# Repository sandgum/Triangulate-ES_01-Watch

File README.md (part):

# Triangulate ES_01 E-ink Watch

---

An ultra-thin ESP32S3-based smartwatch (at just 5mm thick at its thickest point) which uses an E-ink display and two OLEDs to display information while consuming a small amount of power. The main E-ink panel is touch-enabled, with the two additional OLED panels above and below it displaying auxiliary information, such as notifications, background activities etc. 
The watch has built-in heart rate and spO2 sensing via an Analog Devices MAX30102, high-precision smart movement sensing via a Bosch BH260AP IMU and a Bosch BMP585 barometric pressure sensor.

*ACKNOWLEDGMENT: Most of the materials and the human hand model you see in the renders are not my own work, but is Royalty-free or CC0 licensed work legitimately downloaded from BlenderKit using their free plan*

---

To top it all off, the ES_01 is completely workout-friendly, with rubberised sides and no pesky side buttons that get pressed mid-pushup (Every physical input is at the top of the watch)!
The watch features a sleek design, with each component being laid out single file and in its own separate segment of the watch. These segments can all bend around the watch, preserving a uniform thickness all around, which also adds the benefit of being aesthetically pleasing.
The main microcontroller running the watch is an Espressif ESP32-S3 running with Bluetooth LE capabilities, which also allow for it to sync with a smartphone to relay notifications, workout, and weather data etc. through firmware based on ESP-IDF and host smartphone software for iPhone based on Swift (Coming soon, and Android support will come later!)

---

## PCB:

- 4 layers
- Flex PCB
- Single-sided component placement
- 0.2mm board thickness
- Added 0.1mm FR4 stiffeners
- All resistors and capacitors are 0402 size

### Schematics:

### PCB Layout and render:

*Render is out of date*

---

## Enclosure:

- Main cases and top plates of each segment 3D printed using PLA
- Bottom plates for OLED segments are CNC machined from 6061 Aluminium by JLCCNC (can substitute with any rigid material or also with SLA/MSLA printed resin)
- Bottom plate for main E-ink segment 3D printed using an SLM printer in 316L stainless steel (can substitute with other rigid metal with high thermal conductivity)
- Side flexible pieces printed in TPU by an FDM 3D printer

---

## Assembly instructions:

### To manufacture the PCB, refer to the instructions [here](PCB/README.md)

1. Use the solder stencil to squeegee solder paste onto main PCB
2. Place each component onto its respective pads on the main PCB
3. Use a hotplate or a reflow oven to reflow the solder paste underneath the components
4. Hand-solder a thin insulated wire (enamel insulated or rubber insulated) connecting the pads "BATT1_WIRE" together on the PCB
5. Create a solder bridge connecting the pads "GND_TO_GNDIO" and "GNDIO_TO_GND"
6. Create a solder bridge connecting the pads "GND_TO_GNDPWR" and "GNDPWR_TO_GND"
7. Assemble the two "end battery" segments by threading battery wires through them, placing the battery in and attaching the top plates to their respective main cases with superglue
8. Assemble the other battery segment and the haptic module segment in the same way, but thread the "end battery" wires through the dedicated channels in these segments, you should have two sets of two segments with four wires coming out of each set of segments
9. Take the main cases of the OLED modules and superglue the OLED displays into the top of each, making sure the flex cables poke through their dedicated holes
10. Do the same with the E-ink segment and the E-ink display
11. Attach each remaining top plate to its respective main case using superglue
12. Place and superglue the main Flex PCB into the bottom of the E-ink segment and the two OLED segments. The back of the PCB should face the displays
13. Thread the wires from the two sets of segments from step 8 through the holes in the side of the OLED modules and hand-solder the wires onto their respective pads
14. Plug in the flex cables from each display into thir respective FPC connectors on the main PCB
15. Superglue the bottom panels for the OLED segments onto their respective main cases
16. Apply thermal paste on the ESP32-S3 chip on the main PCB
17. Superglue threaded inserts in the two dedicated holes in the corners of the bottom panel for the E-ink segment
18. Superglue the bottom panel to the main case of the E-ink segment
19. Screw two screws into the holes in the top case of the E-ink segment until they mesh with the threaded inserts from the previous step
20. Take two more screws and cut off their entire threaded sections until just the heads remain. Superglue those heads in the holes in the other two corners of the top panel of the E-ink segment
21. Superglue the side TPU pieces to the sides of all the segments
22. Plug in a patch antenna into the exposed U.FL port on the back of the watch, guide the cable through its designated groove, and stick the patch antenna somewhere on the watch

---

## Bill of materials:

### Electronic Components: (Order quantities account for minimum order quantity of parts from the chosen retailer)

| Manufacturer Part Number | Mfr.                        | Order Qty. | Unit Price(USD) | Ext.Price(USD) | Package                                | Description                                                                                                                | Product Link                                                                                                                                                                                                                                                                                                                                                                                                                                                                                                                                                                                                                                                                                                                                                                                                                                                    |
| ------------------------ | --------------------------- | ---------- | --------------- | -------------- | -------------------------------------- | -------------------------------------------------------------------------------------------------------------------------- | --------------------------------------------------------------------------------------------------------------------------------------------------------------------------------------------------------------------------------------------------------------------------------------------------------------------------------------------------------------------------------------------------------------------------------------------------------------------------------------------------------------------------------------------------------------------------------------------------------------------------------------------------------------------------------------------------------------------------------------------------------------------------------------------------------------------------------------------------------------- |
| CC0402JRNPO9BN110        | YAGEO                       | 100        | 0.0013          | 0.13           | 0402                                   | 11pF �5% 50V Ceramic Capacitor NP0 0402                                                                                    | https://www.lcsc.com/product-detail/C527000.html                                                                                                                                                                                                                                                                                                                                                                                                                                                                                                                                                                                                                                                                                                                                                                                                                |
| GRM155R61E475ME15D       | muRata                      | 20         | 0.0403          | 0.81           | 0402                                   | 4.7uF �20% 25V Ceramic Capacitor X5R 0402                                                                                  | https://www.lcsc.com/product-detail/C2858031.html                                                                                                                                                                                                                                                                                                                                                                                                                                                                                                                                                                                                                                                                                                                                                                                                               |
| ESP32-S3                 | ESPRESSIF                   | 1          | 3.0048          | 3              | QFN-56-EP(7x7)                         | -98.4dBm 150Mbps 2.412GHz~2.484GHz 2.4GHz 3V~3.6V QFN-56-EP(7x7) RF Transceiver ICs RoHS                                   | https://www.lcsc.com/product-detail/C2913192.html                                                                                                                                                                                                                                                                                                                                                                                                                                                                                                                                                                                                                                                                                                                                                                                                               |
| 2328702-6                | TE Connectivity             | 5          | 0.2027          | 1.01           | SMD,P=0.5mm,Surface Mount,Right Angle  | FFC/FPC Connector 6 Position 0.5mm Pitch Double-Sided Contacts, Top and Bottom Entry Surface Mount, Right Angle -40?~+85?  | https://www.lcsc.com/product-detail/C3151647.html                                                                                                                                                                                                                                                                                                                                                                                                                                                                                                                                                                                                                                                                                                                                                                                                               |
| FFC2B28-24-G             | Global Connector Technology | 1          | 0.5754          | 0.58           | SMD,P=0.5mm,Surface Mount,Right Angle  | FFC/FPC Connector 24 Position 0.5mm Pitch Double-Sided Contacts, Top and Bottom Entry Surface Mount, Right Angle -25?~+85? | https://www.lcsc.com/product-detail/C3151659.html                                                                                                                                                                                                                                                                                                                                                                                                                                                                                                                                                                                                                                                                                                                                                                                                               |
| BHI260AP                 | Bosch                       | 1          | 9.8338          | 9.83           | LGA-44                                 | LGA-44 IMUs (Inertial Measurement Units) RoHS                                                                              | https://www.lcsc.com/product-detail/C3288651.html                                                                                                                                                                                                                                                                                                                                                                                                                                                                                                                                                                                                                                                                                                                                                                                                               |
| SI1308EDL-T1-GE3         | VISHAY                      | 5          | 0.1543          | 0.77           | SOT-323                                | N-Channel 30V 1.5A 0.4W Surface Mount SOT-323                                                                              | https://www.lcsc.com/product-detail/C469327.html                                                                                                                                                                                                                                                                                                                                                                                                                                                                                                                                                                                                                                                                                                                                                                                                                |
| XC6206P302MR             | HXY MOSFET                  | 50         | 0.0176          | 0.88           | SOT-23                                 | Linear Voltage Regulator IC Positive Fixed 1 Output 300mA SOT-23                                                           | https://www.lcsc.com/product-detail/C5148691.html                                                                                                                                                                                                                                                                                                                                                                                                                                                                                                                                                                                                                                                                                                                                                                                                               |
| MBR0530                  | Huixin                      | 20         | 0.0296          | 0.59           | SOD-123                                | 5.5A 1 Independent 30V 500mV@500mA 500mA SOD-123 Single Diodes RoHS                                                        | https://www.lcsc.com/product-detail/C49435625.html                                                                                                                                                                                                                                                                                                                                                                                                                                                                                                                                                                                                                                                                                                                                                                                                              |
| 0402WGF1004TCE           | UNI-ROYAL                   | 100        | 0.0008          | 0.08           | 0402                                   | 1M? �1% 62.5mW 0402 Thick Film Resistor                                                                                    | https://www.lcsc.com/product-detail/C26083.html                                                                                                                                                                                                                                                                                                                                                                                                                                                                                                                                                                                                                                                                                                                                                                                                                 |
| CL05A105KA5NQNC          | Samsung Electro-Mechanics   | 100        | 0.0033          | 0.33           | 0402                                   | 1uF �10% 25V Ceramic Capacitor X5R 0402                                                                                    | https://www.lcsc.com/product-detail/C52923.html                                                                                                                                                                                                                                                                                                                                                                                                                                                                                                                                                                                                                                                                                                                                                                                                                 |
| XL2EL89CPI-111YLC-40M    | YXC Crystal Oscillators     | 10         | 0.0619          | 0.62           | SMD3225-4P                             | Crystal 40MHz �10ppm 15pF SMD3225-4P                                                                                       | https://www.lcsc.com/product-detail/C5444549.html                                                                                                                                                                                                                                                                                                                                                                                                                                                                                                                                                                                                                                                                                                                                                                                                               |
| TS-1088-AR02016          | XUNPU                       | 10         | 0.0455          | 0.46           | SMD,4x3mm                              | Tactile Switch SPST 160gf 2mm SMD (SMT) Tab 4mm x 3mm Surface Mount                                                        | https://www.lcsc.com/product-detail/C720477.html                                                                                                                                                                                                                                                                                                                                                                                                                                                                                                                                                                                                                                                                                                                                                                                                                |
| BSS138                   | R+O                         | 50         | 0.0172          | 0.86           | SOT-23                                 | N-Channel 50V 340mA 350mW Surface Mount SOT-23                                                                             | https://www.lcsc.com/product-detail/C7420339.html                                                                                                                                                                                                                                                                                                                                                                                                                                                                                                                                                                                                                                                                                                                                                                                                               |
| TCR2EF33,LM(CT           | TOSHIBA                     | 5          | 0.1077          | 0.54           | TSOT-25                                | 3.3V 5.5V Positive Fixed TSOT-25 Voltage Regulators - Linear, Low Drop Out (LDO) Regulators RoHS                           | https://www.lcsc.com/product-detail/C843273.html                                                                                                                                                                                                                                                                                                                                                                                                                                                                                                                                                                                                                                                                                                                                                                                                                |
| LQG15HS3N3S02D           | muRata                      | 100        | 0.0079          | 0.79           | 0402                                   | 800mA 3.3nH 170m? Multilayer inductor 0402 Fixed Inductors RoHS                                                            | https://www.lcsc.com/product-detail/C86064.html                                                                                                                                                                                                                                                                                                                                                                                                                                                                                                                                                                                                                                                                                                                                                                                                                 |
| MRA4003T3G               | onsemi                      | 10         | 0.1152          | 1.15           | SMA(DO-214AC)                          | Diode 300V 1A Surface Mount SMA(DO-214AC)                                                                                  | https://www.lcsc.com/product-detail/C94410.html                                                                                                                                                                                                                                                                                                                                                                                                                                                                                                                                                                                                                                                                                                                                                                                                                 |
| DRV2605LDGSR             | TI                          | 1          | 1.3734          | 1.37           | VSSOP-10-0.5mm                         | I2C VSSOP-10-0.5mm Motor Drivers, Controllers RoHS                                                                         | https://www.lcsc.com/product-detail/C527464.html                                                                                                                                                                                                                                                                                                                                                                                                                                                                                                                                                                                                                                                                                                                                                                                                                |
| LQG15HS2N0S02D           | muRata                      | 100        | 0.0084          | 0.84           | 0402                                   | 900mA 2nH 100m? Multilayer inductor 0402 Fixed Inductors RoHS                                                              | https://www.lcsc.com/product-detail/C18216.html                                                                                                                                                                                                                                                                                                                                                                                                                                                                                                                                                                                                                                                                                                                                                                                                                 |
| 0402WGF5603TCE           | UNI-ROYAL                   | 100        | 0.0006          | 0.06           | 0402                                   | 560k? �1% 62.5mW 0402 Thick Film Resistor                                                                                  | https://www.lcsc.com/product-detail/C132339.html                                                                                                                                                                                                                                                                                                                                                                                                                                                                                                                                                                                                                                                                                                                                                                                                                |
| CL05B103KB5NNNC          | Samsung Electro-Mechanics   | 100        | 0.0014          | 0.14           | 0402                                   | 10nF �10% 50V Ceramic Capacitor X7R 0402                                                                                   | https://www.lcsc.com/product-detail/C15195.html                                                                                                                                                                                                                                                                                                                                                                                                                                                                                                                                                                                                                                                                                                                                                                                                                 |
| 0402B102K500NT           | FH                          | 100        | 0.0012          | 0.12           | 0402                                   | 1nF �10% 50V Ceramic Capacitor X7R 0402                                                                                    | https://www.lcsc.com/product-detail/C1523.html                                                                                                                                                                                                                                                                                                                                                                                                                                                                                                                                                                                                                                                                                                                                                                                                                  |
| CL05B104KO5NNNC          | Samsung Electro-Mechanics   | 100        | 0.0013          | 0.13           | 0402                                   | 100nF �10% 16V Ceramic Capacitor X7R 0402                                                                                  | https://www.lcsc.com/product-detail/C1525.html                                                                                                                                                                                                                                                                                                                                                                                                                                                                                                                                                                                                                                                                                                                                                                                                                  |
| 0402CG1R0C500NT          | FH                          | 100        | 0.0012          | 0.12           | 0402                                   | 1pF 50V Ceramic Capacitor C0G 0402                                                                                         | https://www.lcsc.com/product-detail/C1550.html                                                                                                                                                                                                                                                                                                                                                                                                                                                                                                                                                                                                                                                                                                                                                                                                                  |
| CL05A106MQ5NUNC          | Samsung Electro-Mechanics   | 100        | 0.0056          | 0.56           | 0402                                   | 10uF �20% 6.3V Ceramic Capacitor X5R 0402                                                                                  | https://www.lcsc.com/product-detail/C15525.html                                                                                                                                                                                                                                                                                                                                                                                                                                                                                                                                                                                                                                                                                                                                                                                                                 |
| CL05B224KO5NNNC          | Samsung Electro-Mechanics   | 100        | 0.0041          | 0.41           | 0402                                   | 220nF �10% 16V Ceramic Capacitor X7R 0402                                                                                  | https://www.lcsc.com/product-detail/C16772.html                                                                                                                                                                                                                                                                                                                                                                                                                                                                                                                                                                                                                                                                                                                                                                                                                 |
| BMP585                   | Bosch                       | 1          | 3.5109          | 3.51           | LGA-9(3.3x3.3)                         | 30Kpa~1.25bar LGA-9(3.3x3.3) Pressure Sensors, Transducers RoHS                                                            | https://www.lcsc.com/product-detail/C18184976.html                                                                                                                                                                                                                                                                                                                                                                                                                                                                                                                                                                                                                                                                                                                                                                                                              |
| LD39200PU33R             | ST                          | 1          | 1.0184          | 1.02           | DFN-6(3x3)                             | 3.3V 6V Positive Fixed DFN-6(3x3) Voltage Regulators - Linear, Low Drop Out (LDO) Regulators RoHS                          | https://www.lcsc.com/product-detail/C222192.html                                                                                                                                                                                                                                                                                                                                                                                                                                                                                                                                                                                                                                                                                                                                                                                                                |
| CL05A475MP5NRNC          | Samsung Electro-Mechanics   | 50         | 0.0055          | 0.28           | 0402                                   | 4.7uF �20% 10V Ceramic Capacitor X5R 0402                                                                                  | https://www.lcsc.com/product-detail/C23733.html                                                                                                                                                                                                                                                                                                                                                                                                                                                                                                                                                                                                                                                                                                                                                                                                                 |
| 0402WGF2201TCE           | UNI-ROYAL                   | 100        | 0.0008          | 0.08           | 0402                                   | 2.2k? �1% 62.5mW 0402 Thick Film Resistor                                                                                  | https://www.lcsc.com/product-detail/C25879.html                                                                                                                                                                                                                                                                                                                                                                                                                                                                                                                                                                                                                                                                                                                                                                                                                 |
| 0402WGF4701TCE           | UNI-ROYAL                   | 100        | 0.0008          | 0.08           | 0402                                   | 4.7k? �1% 62.5mW 0402 Thick Film Resistor                                                                                  | https://www.lcsc.com/product-detail/C25900.html                                                                                                                                                                                                                                                                                                                                                                                                                                                                                                                                                                                                                                                                                                                                                                                                                 |
| ANR4012T470M             | APV                         | 10         | 0.0544          | 0.54           | SMD,4x4mm                              | 500mA 47uH 500mA Magnetic Shielded Inductor �20% SMD,4x4mm Fixed Inductors RoHS                                            | https://www.lcsc.com/product-detail/C7497063.html                                                                                                                                                                                                                                                                                                                                                                                                                                                                                                                                                                                                                                                                                                                                                                                                               |
| MAX30102EFD+T            | MAXIM                       | 1          | 13.0636         | 13.06          | OESIP-14                               | I2C OESIP-14 Specialized Sensors RoHS                                                                                      | https://www.lcsc.com/product-detail/C6454833.html                                                                                                                                                                                                                                                                                                                                                                                                                                                                                                                                                                                                                                                                                                                                                                                                               |
| MAX17048X+T10            | MAXIM                       | 1          | 1.1576          | 1.16           | WLP-8(0.9x1.8)                         | Lithium Battery I2C WLP-8(0.9x1.8) Battery Management RoHS                                                                 | https://www.lcsc.com/product-detail/C7497002.html                                                                                                                                                                                                                                                                                                                                                                                                                                                                                                                                                                                                                                                                                                                                                                                                               |
| 1N4148                   | onsemi                      | 50         | 0.0353          | 1.77           | DO-35                                  | Diode 100V 200mA Through Hole DO-35                                                                                        | https://www.lcsc.com/product-detail/C258182.html                                                                                                                                                                                                                                                                                                                                                                                                                                                                                                                                                                                                                                                                                                                                                                                                                |
| FRC0402F1001TS           | FOJAN                       | 100        | 0.0006          | 0.06           | 0402                                   | 1k? �1% 62.5mW 0402 Thick Film Resistor                                                                                    | https://www.lcsc.com/product-detail/C2906864.html                                                                                                                                                                                                                                                                                                                                                                                                                                                                                                                                                                                                                                                                                                                                                                                                               |
| FRC0402F22R0TS           | FOJAN                       | 100        | 0.0006          | 0.06           | 0402                                   | 22? �1% 62.5mW 0402 Thick Film Resistor                                                                                    | https://www.lcsc.com/product-detail/C2929994.html                                                                                                                                                                                                                                                                                                                                                                                                                                                                                                                                                                                                                                                                                                                                                                                                               |
| FRC0402F2R20TS           | FOJAN                       | 100        | 0.0008          | 0.08           | 0402                                   | 2.2? �1% 62.5mW 0402 Thick Film Resistor                                                                                   | https://www.lcsc.com/product-detail/C2909330.html                                                                                                                                                                                                                                                                                                                                                                                                                                                                                                                                                                                                                                                                                                                                                                                                               |
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
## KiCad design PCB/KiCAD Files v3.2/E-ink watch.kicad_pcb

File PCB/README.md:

# How to Manufacture the PCB

1. Go to the folder `PCB/Production Files`

2. Find the zip file named `ES_01_mainPCB-vxx.zip`

3. Upload the zip file to JLCPCB (or your preferred PCB manufacturing site), DO NOT expand the file

4. If you are using JLCPCB, follow these next instructions:
   
   1. **Set Base Material to Flex**
   
   2. Set Substrate Type to 25um dielectric thickness
   
   3. **Set Layers to 4**
   
   4. Leave Dimensions unchanged (They should be greyed out anyways)
   
   5. **Set PCB Qty to 5**
   
   6. Leave Different Design and Delivery Format unchanged
   
   7. **Set PCB Thickness to 0.2mm**
   
   8. Set Coverlay Color to whatever you want! (Yellow is the cheapest btw)
   
   9. Leave Silkscreen, Copper Type, Surface Finish and Gold Thickness unchanged
   
   10. Leave Outer Copper Weight, Inner Copper Weight, Specify Layer Sequence, Stackup Type, Layer Stackup, Coverlay Thickness and Gold Fingers unchanged
   
   11. Set EDA Software to Other
   
   12. **Set Stiffener to FR4**
   
   13. **Set FR4 Thickness to 0.1mm**
   
   14. Leave Cutting Method and Confirm Production file unchanged
   
   15. Set Mark on PCB to Order Number
   
   16. Leave everything else unchanged
   
   17. At the very bottom, select PCB Stencil. In its settings:
       
       1. Leave Framework, Step Stencil and Nano-coating unchanged
       
       2. **Set Stencil Style to Top only**
       
       3. Leave Dimensions unchanged
       
       4. **Set Stencil Qty to 1**
       
       5. Leave everything else unchanged
   
   18. Click Save to Cart, and you're done!

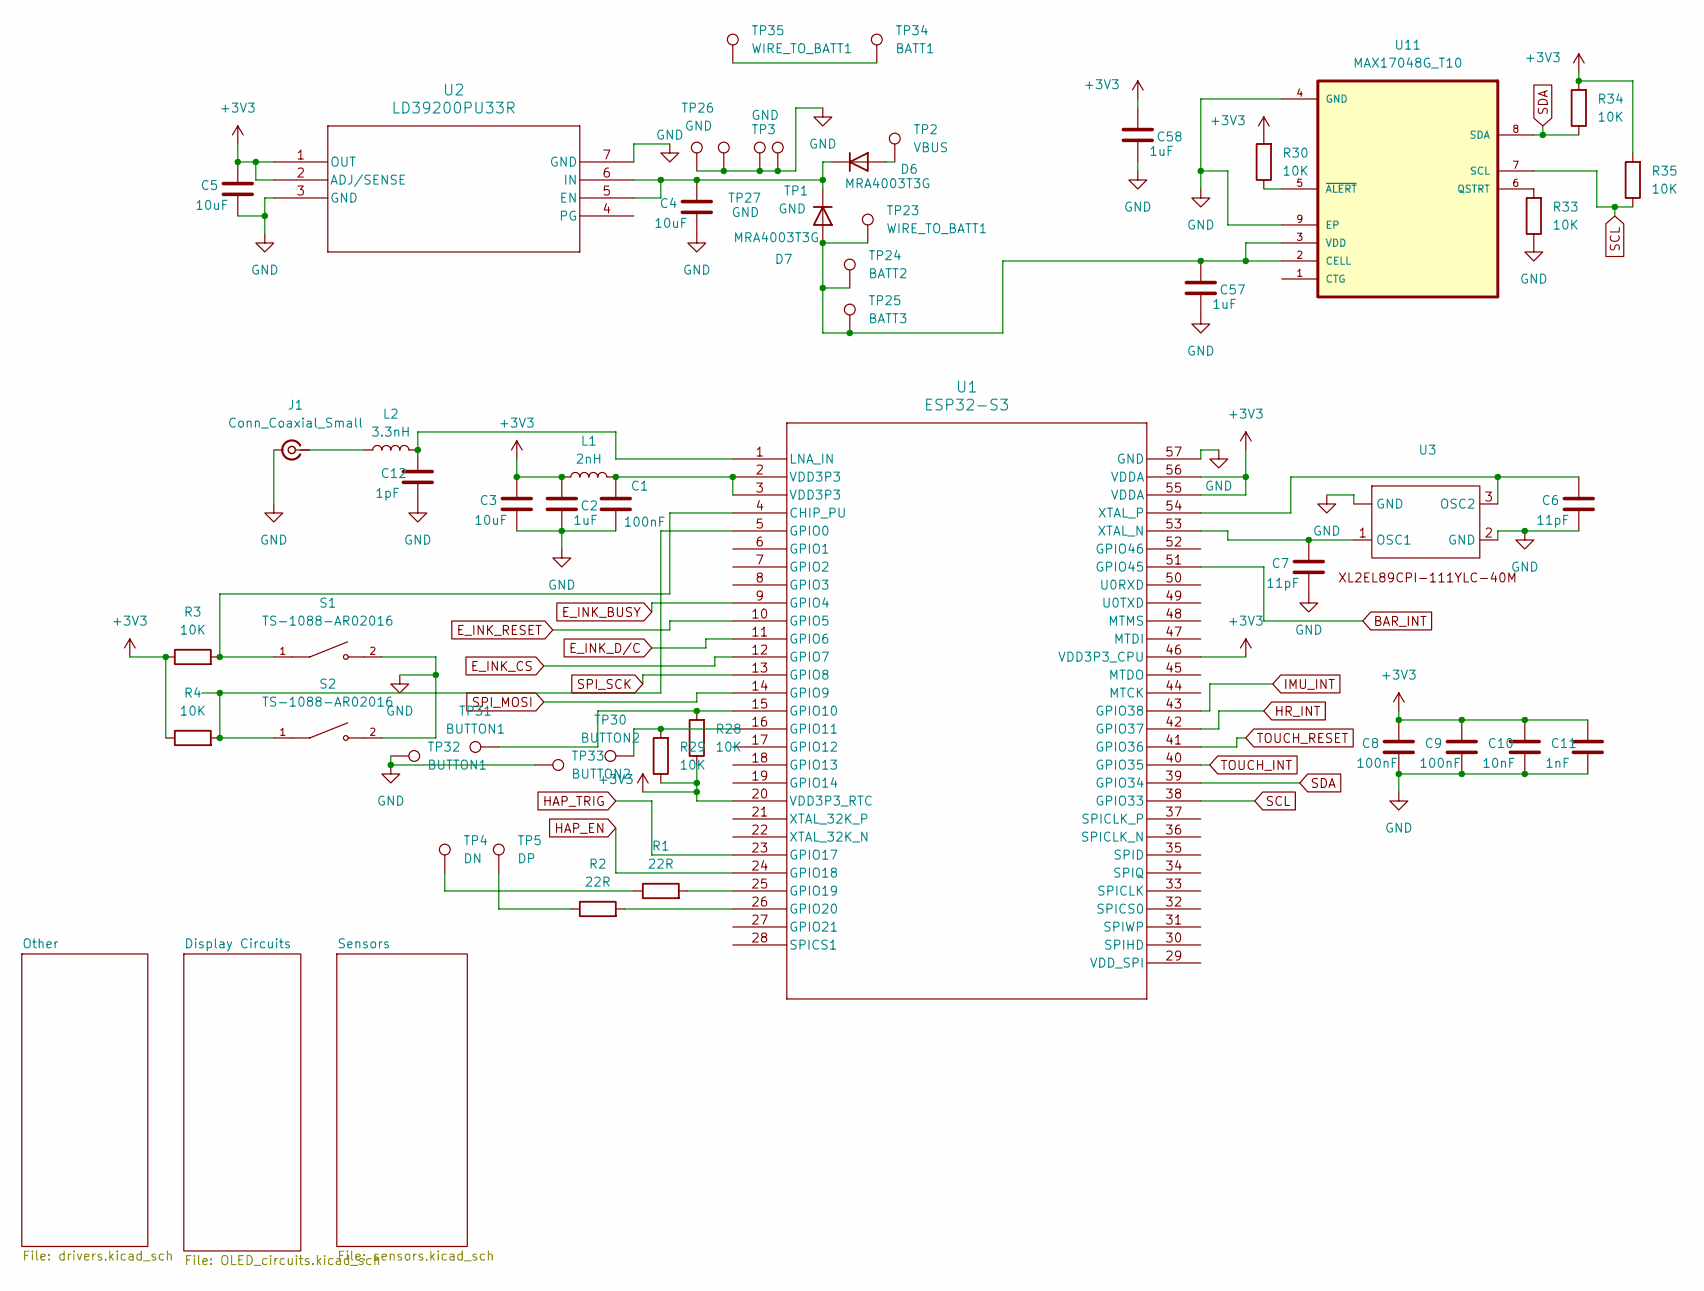
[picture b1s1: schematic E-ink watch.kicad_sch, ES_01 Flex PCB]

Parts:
C1, C8, C9: 100nF; C_0402_1005Metric_Pad0.74x0.62mm_HandSolder
C2, C57, C58: 1uF; C_0402_1005Metric_Pad0.74x0.62mm_HandSolder
C3, C4, C5: 10uF; C_0402_1005Metric_Pad0.74x0.62mm_HandSolder
C6, C7: 11pF; C_0402_1005Metric_Pad0.74x0.62mm_HandSolder
C10: 10nF; C_0402_1005Metric_Pad0.74x0.62mm_HandSolder
C11: 1nF; C_0402_1005Metric_Pad0.74x0.62mm_HandSolder
C12: 1pF; C_0402_1005Metric_Pad0.74x0.62mm_HandSolder
D6, D7: MRA4003T3G; D_SMA
J1: Conn_Coaxial_Small; U.FL_Hirose_U.FL-R-SMT-1_Vertical
L1: 2nH; L_0402_1005Metric_Pad0.77x0.64mm_HandSolder
L2: 3.3nH; L_0402_1005Metric_Pad0.77x0.64mm_HandSolder
R1, R2: 22R; R_0402_1005Metric_Pad0.72x0.64mm_HandSolder
R3, R4, R28, R29, R30, R33, R34, R35: 10K; R_0402_1005Metric_Pad0.72x0.64mm_HandSolder
S1, S2: TS-1088-AR02016; SW_TS-1088-AR02016; PARTREV N/A
TP1, TP3, TP26, TP27: GND; TestPoint_Pad_1.5x1.5mm
TP2: VBUS; TestPoint_Pad_1.5x1.5mm
TP4: DN; TestPoint_Pad_1.5x1.5mm
TP5: DP; TestPoint_Pad_1.5x1.5mm
TP23, TP35: WIRE_TO_BATT1; TestPoint_Pad_1.5x1.5mm
TP24: BATT2; TestPoint_Pad_1.5x1.5mm
TP25: BATT3; TestPoint_Pad_1.5x1.5mm
TP30, TP33: BUTTON2; TestPoint_Pad_1.5x1.5mm
TP31, TP32: BUTTON1; TestPoint_Pad_1.5x1.5mm
TP34: BATT1; TestPoint_Pad_1.5x1.5mm
U1: ESP32-S3; QFN56_7X7_EXP
U2: LD39200PU33R; SON_DFN6_3X3_STM
U3: Untitled
U11: MAX17048G_T10; SON50P200X200X80-9N

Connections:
+3V3: C2.1, C3.1, C5.1, C8.1, C9.1, C10.1, C11.1, C58.1, L1.1, R3.1, R4.1, R28.1, R29.1, R30.2, R34.2, R35.2, U1.20 (VDD3P3_RTC), U1.46 (VDD3P3_CPU), U1.55 (VDDA), U1.56 (VDDA), U2.1 (OUT), U2.2 (ADJ/SENSE); also elsewhere on the board
BAR_INT: U1.51 (GPIO45); also elsewhere on the board
E_INK_BUSY: U1.9 (GPIO4); also elsewhere on the board
E_INK_CS: U1.12 (GPIO7); also elsewhere on the board
E_INK_D/C: U1.11 (GPIO6); also elsewhere on the board
E_INK_RESET: U1.10 (GPIO5); also elsewhere on the board
GND: C1.2, C2.2, C3.2, C4.2, C5.2, C6.2, C7.2, C8.2, C9.2, C10.2, C11.2, C12.2, C57.2, C58.2, J1.2 (Ext), R33.1, S1.2, S2.2, TP1.1, TP3.1, TP26.1, TP27.1, TP32.1, TP33.1, U1.57 (GND), U2.3 (GND), U2.7 (GND), U3. (GND), U3.2 (GND), U11.4 (GND), U11.9 (EP); also elsewhere on the board
HAP_EN: U1.24 (GPIO18); also elsewhere on the board
HAP_TRIG: U1.23 (GPIO17); also elsewhere on the board
HR_INT: U1.42 (GPIO37); also elsewhere on the board
IMU_INT: U1.43 (GPIO38); also elsewhere on the board
unnamed: C1.1, L1.2, U1.2 (VDD3P3), U1.3 (VDD3P3)
unnamed: D6.2 (A), TP2.1
unnamed: C4.1, D6.1 (K), D7.1 (K), U2.5 (EN), U2.6 (IN)
unnamed: C57.1, D7.2 (A), TP23.1, TP24.1, TP25.1, U11.2 (CELL), U11.3 (VDD)
unnamed: J1.1 (In), L2.1
unnamed: R1.1, TP4.1
unnamed: R2.1, TP5.1
unnamed: TP34.1, TP35.1
unnamed: R3.2, S1.1, U1.4 (CHIP_PU)
unnamed: R4.2, S2.1, U1.5 (GPIO0)
unnamed: R28.2, TP31.1, U1.15 (GPIO10)
unnamed: R29.2, TP30.1, U1.16 (GPIO11)
unnamed: R1.2, U1.25 (GPIO19)
unnamed: R2.2, U1.26 (GPIO20)
unnamed: C12.1, L2.2, U1.1 (LNA_IN)
unnamed: C7.1, U1.53 (XTAL_N), U3.1 (OSC1)
unnamed: C6.1, U1.54 (XTAL_P), U3.3 (OSC2)
unnamed: R33.2, U11.6 (QSTRT)
unnamed: R30.1, U11.5 (~ALERT)
SCL: R35.1, U1.38 (GPIO33), U11.7 (SCL); also elsewhere on the board
SDA: R34.1, U1.39 (GPIO34), U11.8 (SDA); also elsewhere on the board
SPI_MOSI: U1.14 (GPIO9); also elsewhere on the board
SPI_SCK: U1.13 (GPIO8); also elsewhere on the board
TOUCH_INT: U1.40 (GPIO35); also elsewhere on the board
TOUCH_RESET: U1.41 (GPIO36); also elsewhere on the board

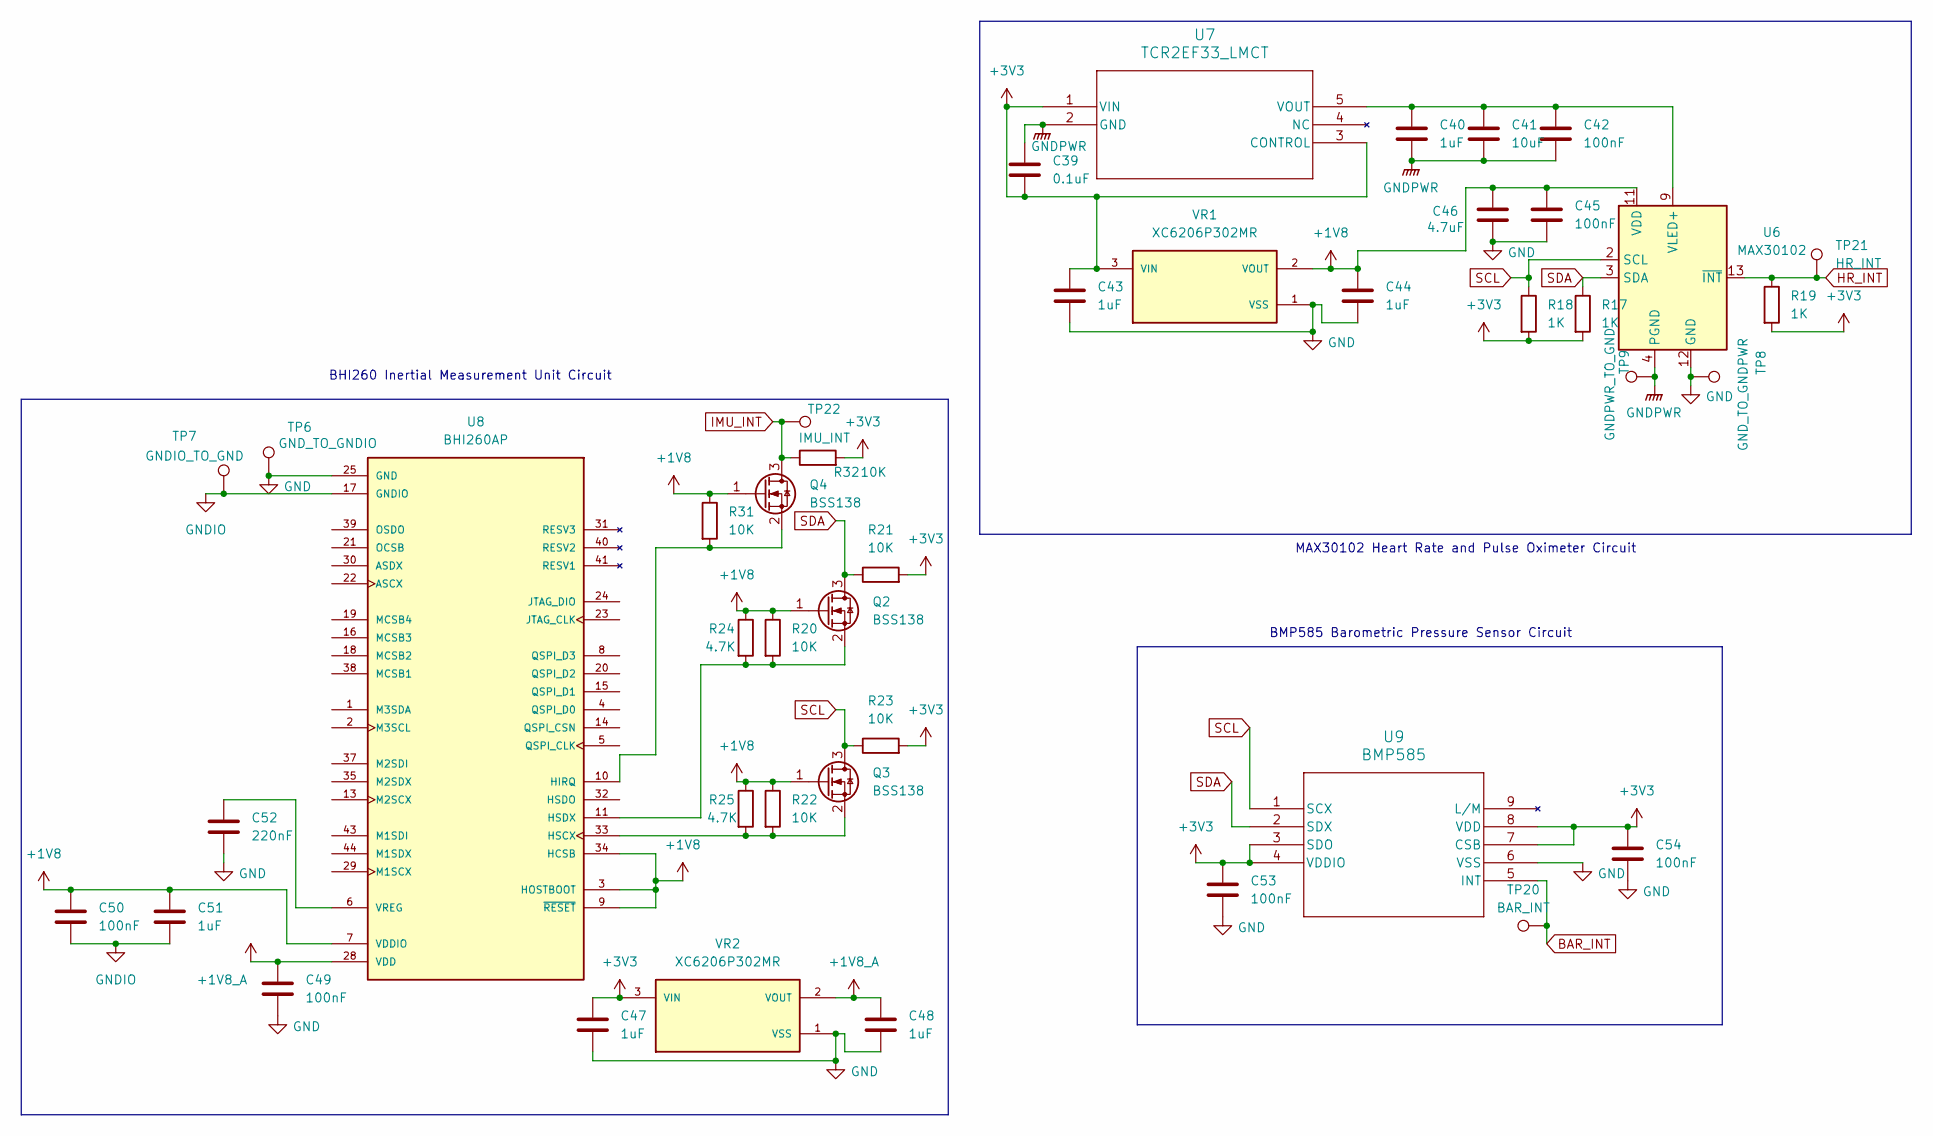
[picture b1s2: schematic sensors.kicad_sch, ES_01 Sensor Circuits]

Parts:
C39: 0.1uF; C_0402_1005Metric_Pad0.74x0.62mm_HandSolder
C40, C43, C44, C47, C48, C51: 1uF; C_0402_1005Metric_Pad0.74x0.62mm_HandSolder
C41: 10uF; C_0402_1005Metric_Pad0.74x0.62mm_HandSolder
C42, C45, C49, C50, C53, C54: 100nF; C_0402_1005Metric_Pad0.74x0.62mm_HandSolder
C46: 4.7uF; C_0402_1005Metric_Pad0.74x0.62mm_HandSolder
C52: 220nF; C_0402_1005Metric_Pad0.74x0.62mm_HandSolder
Q2, Q3, Q4: BSS138; SOT-23
R17, R18, R19: 1K; R_0402_1005Metric_Pad0.72x0.64mm_HandSolder
R20, R21, R22, R23, R31, R32: 10K; R_0402_1005Metric_Pad0.72x0.64mm_HandSolder
R24, R25: 4.7K; R_0402_1005Metric_Pad0.72x0.64mm_HandSolder
TP6: GND_TO_GNDIO; TestPoint_Pad_1.5x1.5mm
TP7: GNDIO_TO_GND; TestPoint_Pad_1.5x1.5mm
TP8: GND_TO_GNDPWR; TestPoint_Pad_1.5x1.5mm
TP9: GNDPWR_TO_GND; TestPoint_Pad_1.5x1.5mm
TP20: BAR_INT; TestPoint_Pad_D1.0mm
TP21: HR_INT; TestPoint_Pad_D1.0mm
TP22: IMU_INT; TestPoint_Pad_D1.0mm
U6: MAX30102; Maxim_OLGA-14_3.3x5.6mm_P0.8mm
U7: TCR2EF33_LMCT; SOT-25 SMV_TOS
U8: BHI260AP; XDCR_BHI260AP; PARTREV 1.1
U9: BMP585; LGA9_BMP585_BOS
VR1, VR2: XC6206P302MR; SOT95P280X130-3N; PARTREV N/A

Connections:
+1V8: C44.1, C45.1, C46.1, C50.1, C51.1, Q2.1 (G), Q3.1 (G), Q4.1 (G), R20.1, R22.1, R24.1, R25.1, R31.1, U6.11 (VDD), U8.3 (HOSTBOOT), U8.7 (VDDIO), U8.9 (~RESET), U8.12 (VDDIO), U8.34 (HCSB), U8.42 (VDDIO), VR1.2 (VOUT)
+1V8_A: C48.1, C49.1, U8.28 (VDD), VR2.2 (VOUT)
+3V3: C39.2, C43.1, C47.1, C53.1, C54.1, R17.2, R18.2, R19.2, R21.2, R23.2, R32.2, U7.1 (VIN), U7.3 (CONTROL), U9.3 (SDO), U9.4 (VDDIO), U9.7 (CSB), U9.8 (VDD), VR1.3 (VIN), VR2.3 (VIN); also elsewhere on the board
BAR_INT: TP20.1, U9.5 (INT); also elsewhere on the board
GND: C43.2, C44.2, C45.2, C46.2, C47.2, C48.2, C49.2, C52.2, C53.2, C54.2, TP6.1, TP8.1, U6.12 (GND), U8.25 (GND), U8.26 (GND), U8.27 (GND), U9.6 (VSS), VR1.1 (VSS), VR2.1 (VSS); also elsewhere on the board
GNDIO: C50.2, C51.2, TP7.1, U8.17 (GNDIO), U8.36 (GNDIO)
GNDPWR: C39.1, C40.2, C41.2, C42.2, TP9.1, U6.4 (PGND), U7.2 (GND)
HR_INT: R19.1, TP21.1, U6.13 (~INT); also elsewhere on the board
IMU_INT: Q4.3 (D), R32.1, TP22.1; also elsewhere on the board
unnamed: Q2.2 (S), R20.2, R24.2, U8.11 (HSDX)
unnamed: Q3.2 (S), R22.2, R25.2, U8.33 (HSCX)
unnamed: Q4.2 (S), R31.2, U8.10 (HIRQ)
unnamed: C40.1, C41.1, C42.1, U6.9 (VLED+), U6.10 (VLED+), U7.5 (VOUT)
unnamed: C52.1, U8.6 (VREG)
SCL: Q3.3 (D), R18.1, R23.1, U6.2 (SCL), U9.1 (SCX); also elsewhere on the board
SDA: Q2.3 (D), R17.1, R21.1, U6.3 (SDA), U9.2 (SDX); also elsewhere on the board

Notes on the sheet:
MAX30102 Heart Rate and Pulse Oximeter Circuit
BHI260 Inertial Measurement Unit Circuit
BMP585 Barometric Pressure Sensor Circuit

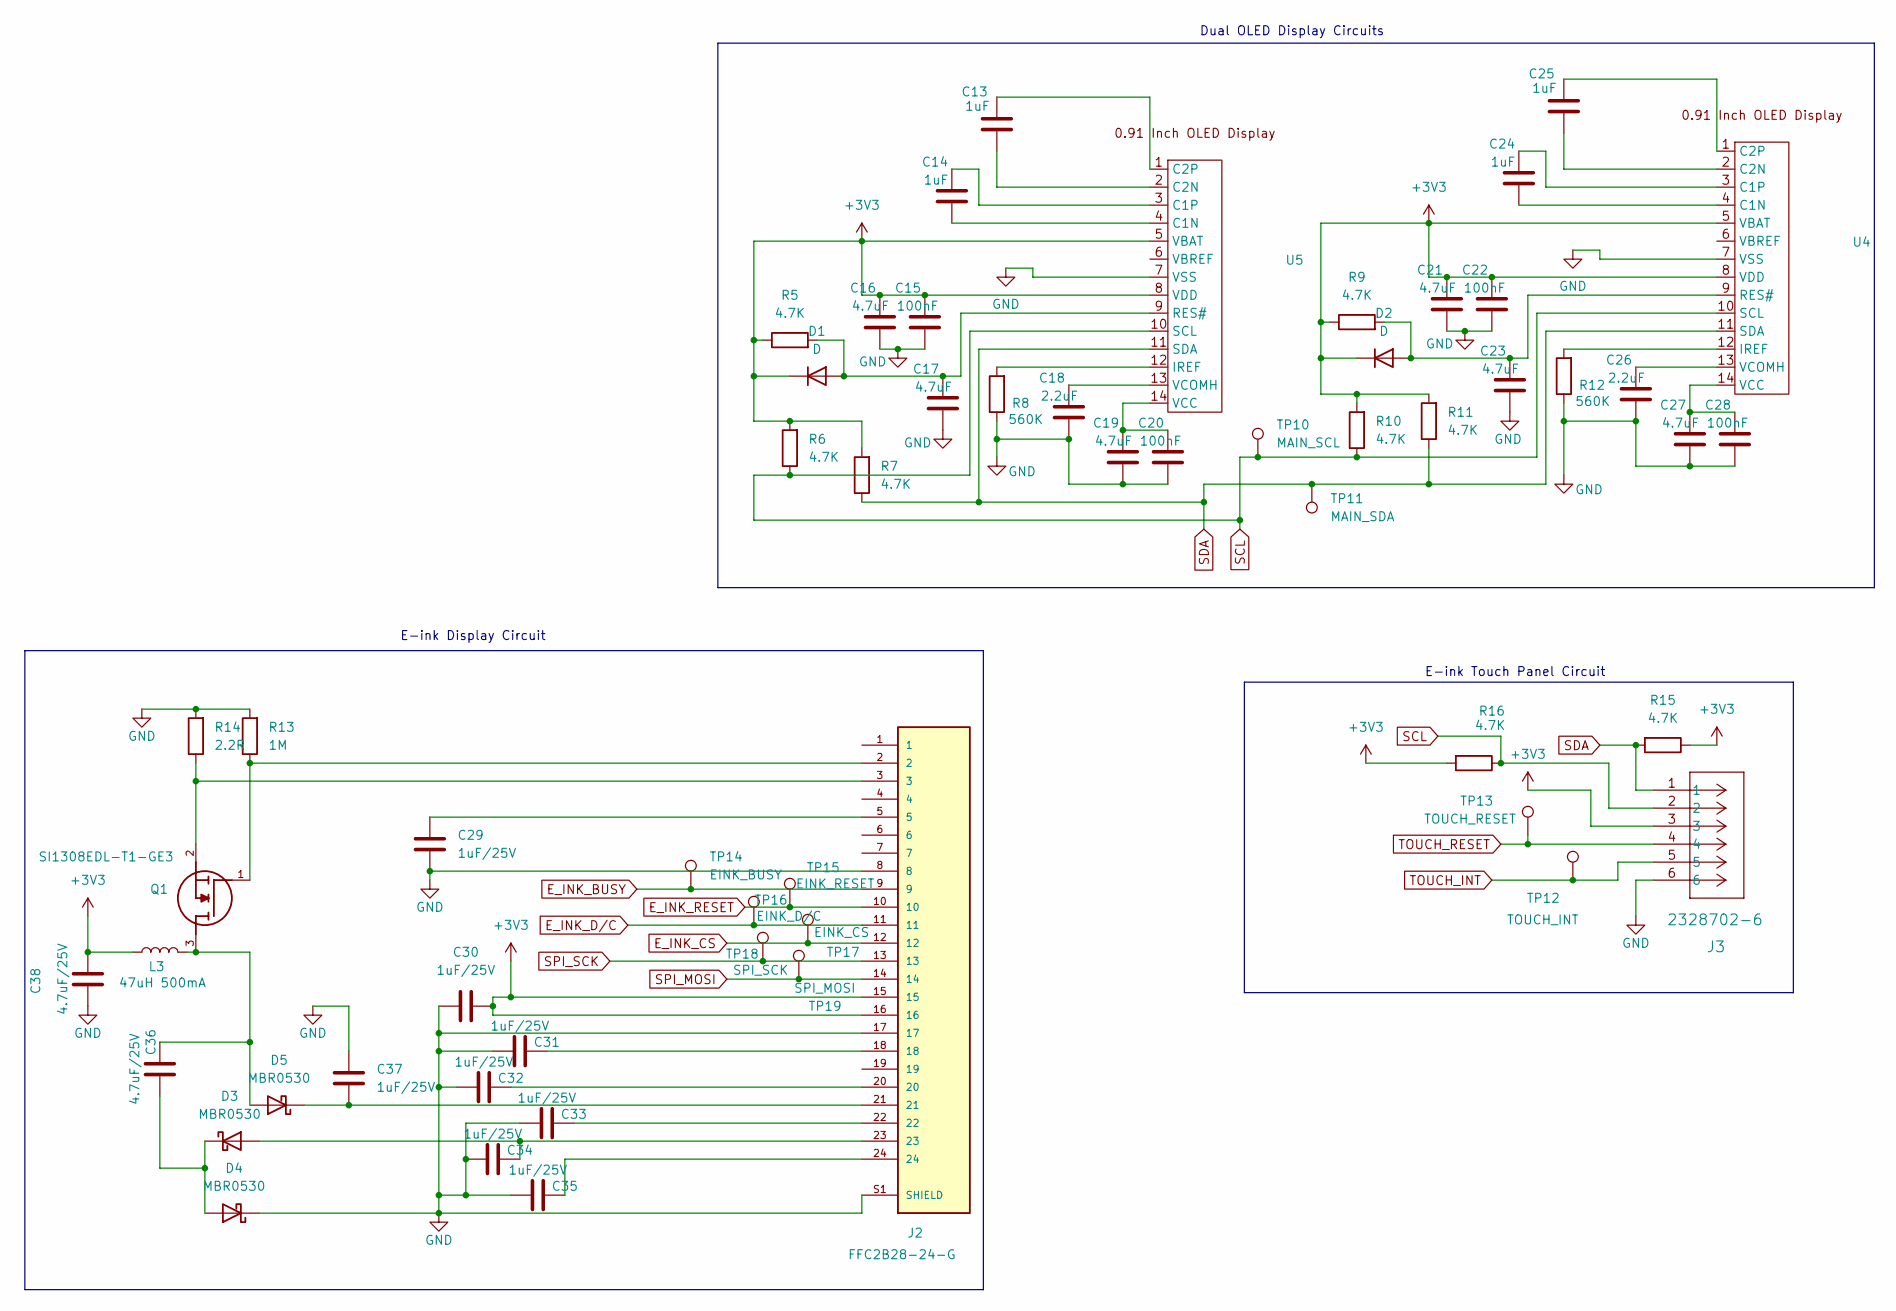
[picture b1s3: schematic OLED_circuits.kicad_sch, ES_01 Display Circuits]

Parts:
C13, C14, C24, C25: 1uF; C_0402_1005Metric_Pad0.74x0.62mm_HandSolder
C15, C20, C22, C28: 100nF; C_0402_1005Metric_Pad0.74x0.62mm_HandSolder
C16, C17, C19, C21, C23, C27: 4.7uF; C_0402_1005Metric_Pad0.74x0.62mm_HandSolder
C18, C26: 2.2uF; C_0402_1005Metric_Pad0.74x0.62mm_HandSolder
C29, C30, C31, C32, C33, C34, C35, C37: 1uF/25V; C_0402_1005Metric_Pad0.74x0.62mm_HandSolder
C36, C38: 4.7uF/25V; C_0402_1005Metric_Pad0.74x0.62mm_HandSolder
D1, D2: D; D_DO-35_SOD27_P7.62mm_Horizontal
D3, D4, D5: MBR0530; D_0805_2012Metric_Pad1.15x1.40mm_HandSolder
J2: FFC2B28-24-G; GCT_FFC2B28-24-G; PARTREV A
J3: 2328702-6; CONN6_2328702-6_TEC
L3: 47uH 500mA; Untitled
Q1: SI1308EDL-T1-GE3; SOT65P210X110-3N; Mouser_Part_Number 78-SI1308EDL-T1-GE3
R5, R6, R7, R9, R10, R11, R15, R16: 4.7K; R_0402_1005Metric_Pad0.72x0.64mm_HandSolder
R8, R12: 560K; R_0402_1005Metric_Pad0.72x0.64mm_HandSolder
R13: 1M; R_0402_1005Metric_Pad0.72x0.64mm_HandSolder
R14: 2.2R; R_0402_1005Metric_Pad0.72x0.64mm_HandSolder
TP10: MAIN_SCL; TestPoint_Pad_D1.0mm
TP11: MAIN_SDA; TestPoint_Pad_D1.0mm
TP12: TOUCH_INT; TestPoint_Pad_D1.0mm
TP13: TOUCH_RESET; TestPoint_Pad_D1.0mm
TP14: EINK_BUSY; TestPoint_Pad_D1.0mm
TP15: EINK_RESET; TestPoint_Pad_D1.0mm
TP16: EINK_D/C; TestPoint_Pad_D1.0mm
TP17: EINK_CS; TestPoint_Pad_D1.0mm
TP18: SPI_SCK; TestPoint_Pad_D1.0mm
TP19: SPI_MOSI; TestPoint_Pad_D1.0mm
U4, U5: Untitled

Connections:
+3V3: C15.1, C16.1, C21.1, C22.1, C30.2, C38.2, D1.1 (K), D2.1 (K), J2.15, J2.16, J3.3, L3.1, R5.1, R6.2, R7.2, R9.1, R10.2, R11.2, R15.1, R16.2, U4.5 (VBAT), U4.8 (VDD), U5.5 (VBAT), U5.8 (VDD); also elsewhere on the board
E_INK_BUSY: J2.9, TP14.1; also elsewhere on the board
E_INK_CS: J2.12, TP17.1; also elsewhere on the board
E_INK_D/C: J2.11, TP16.1; also elsewhere on the board
E_INK_RESET: J2.10, TP15.1; also elsewhere on the board
GND: C15.2, C16.2, C17.2, C18.2, C19.2, C20.2, C21.2, C22.2, C23.2, C26.2, C27.2, C28.2, C29.2, C30.1, C31.1, C32.1, C33.1, C34.1, C35.1, C37.1, C38.1, D4.1 (K), J2.8, J2.17, J2.S1 (SHIELD), J2.S2 (SHIELD), J3.6, R8.1, R12.1, R13.2, R14.2, U4.7 (VSS), U5.7 (VSS); also elsewhere on the board
unnamed: C29.1, J2.5
unnamed: C31.2, J2.18
unnamed: C32.2, J2.20
unnamed: C33.2, J2.22
unnamed: C35.2, J2.24
unnamed: C17.1, D1.2 (A), R5.2, U5.9 (RES#)
unnamed: C23.1, D2.2 (A), R9.2, U4.9 (RES#)
unnamed: C34.2, D3.2 (A), J2.23
unnamed: C36.1, D3.1 (K), D4.2 (A)
unnamed: C36.2, D5.2 (A), L3.2, Q1.3
unnamed: C37.2, D5.1 (K), J2.21
unnamed: J2.2, Q1.1, R13.1
unnamed: J2.3, Q1.2, R14.1
unnamed: C24.2, U4.4 (C1N)
unnamed: C24.1, U4.3 (C1P)
unnamed: C25.2, U4.2 (C2N)
unnamed: C25.1, U4.1 (C2P)
unnamed: R12.2, U4.12 (IREF)
unnamed: C27.1, C28.1, U4.14 (VCC)
unnamed: C26.1, U4.13 (VCOMH)
unnamed: C14.2, U5.4 (C1N)
unnamed: C14.1, U5.3 (C1P)
unnamed: C13.2, U5.2 (C2N)
unnamed: C13.1, U5.1 (C2P)
unnamed: R8.2, U5.12 (IREF)
unnamed: C19.1, C20.1, U5.14 (VCC)
unnamed: C18.1, U5.13 (VCOMH)
SCL: J3.2, R6.1, R10.1, R16.1, TP10.1, U4.10 (SCL), U5.10 (SCL); also elsewhere on the board
SDA: J3.1, R7.1, R11.1, R15.2, TP11.1, U4.11 (SDA), U5.11 (SDA); also elsewhere on the board
SPI_MOSI: J2.14, TP19.1; also elsewhere on the board
SPI_SCK: J2.13, TP18.1; also elsewhere on the board
TOUCH_INT: J3.5, TP12.1; also elsewhere on the board
TOUCH_RESET: J3.4, TP13.1; also elsewhere on the board

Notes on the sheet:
E-ink Display Circuit
Dual OLED Display Circuits
E-ink Touch Panel Circuit

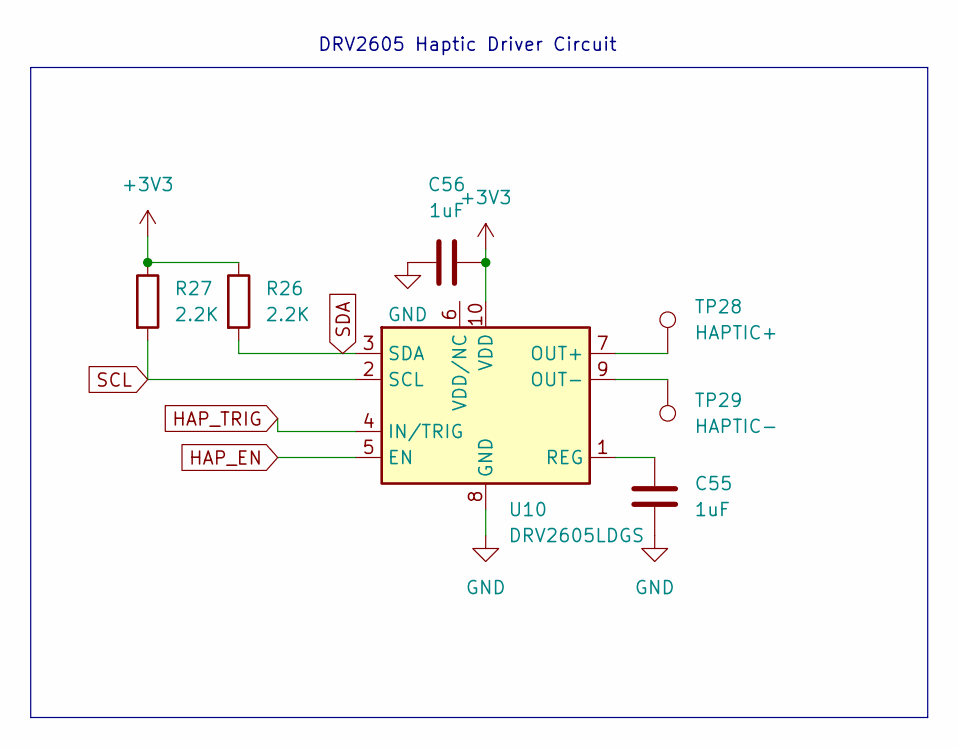
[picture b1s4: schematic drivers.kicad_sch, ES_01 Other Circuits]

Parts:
C55, C56: 1uF; C_0402_1005Metric_Pad0.74x0.62mm_HandSolder
R26, R27: 2.2K; R_0402_1005Metric_Pad0.72x0.64mm_HandSolder
TP28: HAPTIC+; TestPoint_Pad_1.5x1.5mm
TP29: HAPTIC-; TestPoint_Pad_1.5x1.5mm
U10: DRV2605LDGS; VSSOP-10_3x3mm_P0.5mm

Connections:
+3V3: C56.2, R26.1, R27.1, U10.10 (VDD); also elsewhere on the board
GND: C55.2, C56.1, U10.8 (GND); also elsewhere on the board
HAP_EN: U10.5 (EN); also elsewhere on the board
HAP_TRIG: U10.4 (IN/TRIG); also elsewhere on the board
unnamed: TP28.1, U10.7 (OUT+)
unnamed: TP29.1, U10.9 (OUT-)
unnamed: C55.1, U10.1 (REG)
SCL: R27.2, U10.2 (SCL); also elsewhere on the board
SDA: R26.2, U10.3 (SDA); also elsewhere on the board

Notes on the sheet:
DRV2605 Haptic Driver Circuit

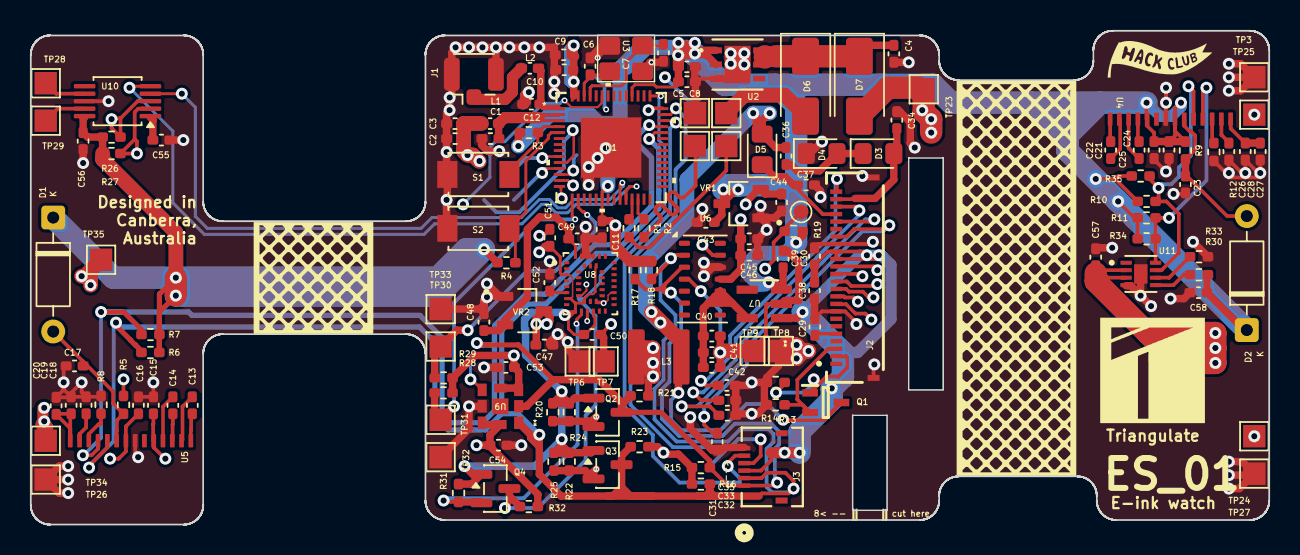
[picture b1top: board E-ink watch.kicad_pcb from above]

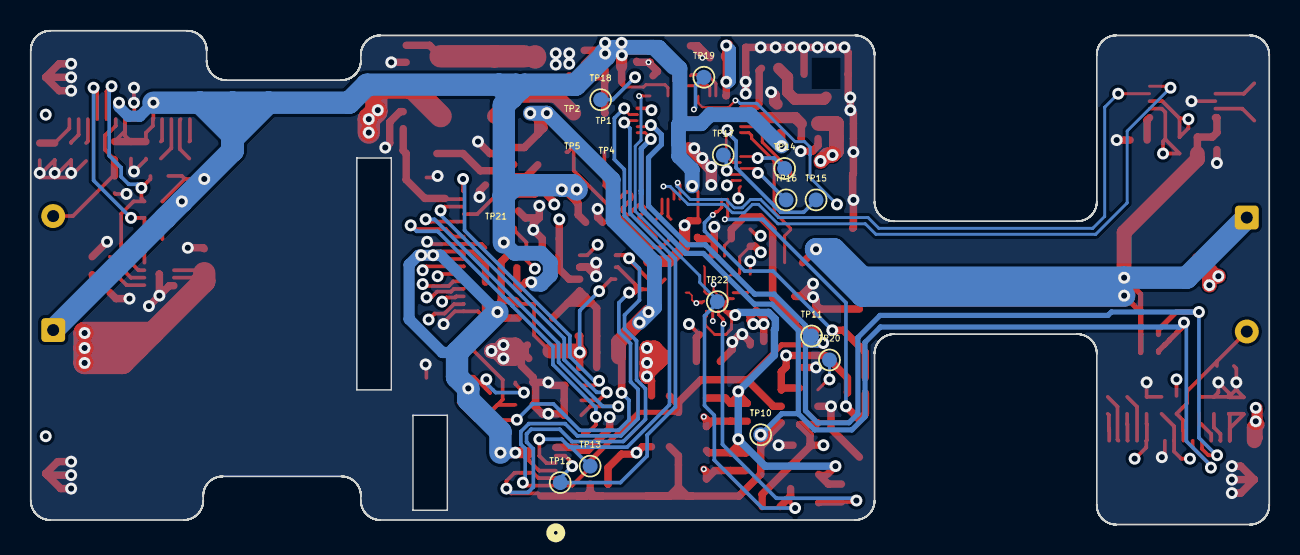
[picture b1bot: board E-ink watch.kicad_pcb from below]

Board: 4 copper layers, 82.8 x 33.0 mm, 160 parts (12 on the bottom side), 75 nets.

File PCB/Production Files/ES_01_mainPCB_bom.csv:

Designator,Footprint,Quantity,Value,LCSC Part #
"C1, C15, C20, C22, C28, C42, C45, C49, C50, C53, C54, C8, C9",0402,13,100nF,
C10,0402,1,10nF,
C11,0402,1,1nF,
C12,0402,1,1pF,
"C13, C14, C2, C24, C25, C40, C43, C44, C47, C48, C51, C55, C56, C57, C58",0402,15,1uF,
"C16, C17, C19, C21, C23, C27, C46",0402,7,4.7uF,
"C18, C26",0402,2,2.2uF,
"C29, C30, C31, C32, C33, C34, C35, C37",0402,8,1uF/25V,
"C3, C4, C41, C5",0402,4,10uF,
"C36, C38",0402,2,4.7uF/25V,
C39,0402,1,0.1uF,
C52,0402,1,220nF,
"C6, C7",0402,2,11pF,
"D1, D2",D_DO-35_SOD27_P7.62mm_Horizontal,2,D,
"D3, D4, D5",0805,3,MBR0530,
"D6, D7",D_SMA,2,MRA4003T3G,
J1,U.FL_Hirose_U.FL-R-SMT-1_Vertical,1,Conn_Coaxial_Small,
J2,GCT_FFC2B28-24-G,1,FFC2B28-24-G,
J3,CONN6_2328702-6_TEC,1,2328702-6,
L1,0402,1,2nH,
L2,0402,1,3.3nH,
L3,Untitled,1,47uH 500mA,
Q1,SOT65P210X110-3N,1,SI1308EDL-T1-GE3,
"Q2, Q3, Q4",SOT-23,3,BSS138,
"R1, R2",0402,2,22R,
"R10, R11, R15, R16, R24, R25, R5, R6, R7, R9",0402,10,4.7K,
"R12, R8",0402,2,560K,
R13,0402,1,1M,
R14,0402,1,2.2R,
"R17, R18, R19",0402,3,1K,
"R20, R21, R22, R23, R28, R29, R3, R30, R31, R32, R33, R34, R35, R4",0402,14,10K,
"R26, R27",0402,2,2.2K,
"S1, S2",SW_TS-1088-AR02016,2,TS-1088-AR02016,
"TP1, TP26, TP27, TP3",TestPoint_Pad_1.5x1.5mm,4,GND,
TP10,TestPoint_Pad_D1.0mm,1,MAIN_SCL,
TP11,TestPoint_Pad_D1.0mm,1,MAIN_SDA,
TP12,TestPoint_Pad_D1.0mm,1,TOUCH_INT,
TP13,TestPoint_Pad_D1.0mm,1,TOUCH_RESET,
TP14,TestPoint_Pad_D1.0mm,1,EINK_BUSY,
TP15,TestPoint_Pad_D1.0mm,1,EINK_RESET,
TP16,TestPoint_Pad_D1.0mm,1,EINK_D/C,
TP17,TestPoint_Pad_D1.0mm,1,EINK_CS,
TP18,TestPoint_Pad_D1.0mm,1,SPI_SCK,
TP19,TestPoint_Pad_D1.0mm,1,SPI_MOSI,
TP2,TestPoint_Pad_1.5x1.5mm,1,VBUS,
TP20,TestPoint_Pad_D1.0mm,1,BAR_INT,
TP21,TestPoint_Pad_D1.0mm,1,HR_INT,
TP22,TestPoint_Pad_D1.0mm,1,IMU_INT,
"TP23, TP35",TestPoint_Pad_1.5x1.5mm,2,WIRE_TO_BATT1,
TP24,TestPoint_Pad_1.5x1.5mm,1,BATT2,
TP25,TestPoint_Pad_1.5x1.5mm,1,BATT3,
TP28,TestPoint_Pad_1.5x1.5mm,1,HAPTIC+,
TP29,TestPoint_Pad_1.5x1.5mm,1,HAPTIC-,
"TP30, TP33",TestPoint_Pad_1.5x1.5mm,2,BUTTON2,
"TP31, TP32",TestPoint_Pad_1.5x1.5mm,2,BUTTON1,
TP34,TestPoint_Pad_1.5x1.5mm,1,BATT1,
TP4,TestPoint_Pad_1.5x1.5mm,1,DN,
TP5,TestPoint_Pad_1.5x1.5mm,1,DP,
TP6,TestPoint_Pad_1.5x1.5mm,1,GND_TO_GNDIO,
TP7,TestPoint_Pad_1.5x1.5mm,1,GNDIO_TO_GND,
TP8,TestPoint_Pad_1.5x1.5mm,1,GND_TO_GNDPWR,
TP9,TestPoint_Pad_1.5x1.5mm,1,GNDPWR_TO_GND,
U1,QFN56_7X7_EXP,1,ESP32-S3,
U10,VSSOP-10_3x3mm_P0.5mm,1,DRV2605LDGS,
U11,SON50P200X200X80-9N,1,MAX17048G_T10,
U2,SON_DFN6_3X3_STM,1,LD39200PU33R,
"U3, U4, U5",Untitled,3,~,
U6,Maxim_OLGA-14_3.3x5.6mm_P0.8mm,1,MAX30102,
U7,SOT-25   SMV_TOS,1,TCR2EF33_LMCT,
U8,XDCR_BHI260AP,1,BHI260AP,
U9,LGA9_BMP585_BOS,1,BMP585,
"VR1, VR2",SOT95P280X130-3N,2,XC6206P302MR,
